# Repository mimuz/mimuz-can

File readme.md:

# mi:muz:can

`mi:muz-can` and variations are small boards for build easier to midi instrument that sounds cans using with push solenoid.

The following variations are exist:

## In Production

- [mi:muz:can (Standard Version)](./mimuz-can): "mi:muz:can" is a board for build easier to USB-MIDI instrument that sounds up to 6 cans using with push solenoid. For using powerful electric current, It has 2.1mm DC Jack for 12V DC Power supply.
- [mi:muz:can-lite](./mimuz-can-lite): "mi:muz:can-lite" is a board for build easier to USB-MIDI instrument that sounds up to 2 cans using with push solenoid. This is a "simple for use" version, It has micro-B usb connector for using USB charger for smartphone/tablet.

## demo

- [1st demo (YouTube)](https://youtu.be/6YQHXj_-I3c)

## Solenoids

All of the mi:muz:can devices are now only support the following 5V PUSH type solenoids:

- [Sparkfun Solenoid - 5v (small) (ROB-11015)](https://www.sparkfun.com/products/11015)
- [ZHO-0420S-05A4.5(5V)](http://akizukidenshi.com/catalog/g/gP-10761/)

## Licenses

- [Licences for mi:muz:can](./mimuz-can/LICENSE.md)
- [Licences for mi:muz:can-lite](./mimuz-can-lite/LICENSE.md)

## [Previous draft versions (Arduino versions)](./draft)

Previous draft versions (Arduino versions) are for experimental use versions made with [Arduino UNO Rev.3](https://store.arduino.cc/arduino-uno-rev3), [Ardiono Leonardo](https://www.arduino.cc/en/main/arduinoBoardLeonardo) and [mi:muz:expr#1](https://github.com/mimuz/mimuz-avr-core/tree/master/boards/expr1).

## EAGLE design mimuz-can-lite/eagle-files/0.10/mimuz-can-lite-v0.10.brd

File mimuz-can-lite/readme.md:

# mi:muz:can-lite

"mi:muz:can-lite" is a board for build easier to USB-MIDI instrument that sounds up to 2 cans using with push solenoid. This is a "simple for use" version, It has micro-B usb connector for using USB charger for smartphone/tablet.

## Version

- v0.10 (2017.05.10)

## Eagle Files

[eagle files (v0.10)](./eagle-files/v0.10)

## parts

- [STM32F042K6T6](http://www.st.com/content/st_com/ja/products/microcontrollers/stm32-32-bit-arm-cortex-mcus/stm32f0-series/stm32f0x2/stm32f042k6.html) * 1
- [HT7333-A (3.3V regulator) SOT89-3](http://www.holtek.com.tw/documents/10179/116711/HT73xx-1v100.pdf) * 1
- [Ferrite beads (0805)](http://akizukidenshi.com/catalog/g/gP-04054/) * 1 [ID1]
- 470Ω(0603) * 1 (For USB DATA LED)
- 1kΩ(0603) * 2 (For FET gate line)
- 1.5kΩ(0805) * 1 (For Power LED)
- 3mLED * 4 
- 0.1uF(0603) * 3
- 22uF(0805) * 1
- 47uF(1206 25V) * 1
- [Tactical Switch (2 points SMT)](http://www.aitendo.com/product/10525) * 1
- [micro USB Connector](https://www.aliexpress.com/item/Free-shipping-100pcs-lot-4-feet-DIP-5P-SMD-Micro-USB-Connector-V8-Port-Charge-Socket/32214653369.html?spm=2114.13010608.0.0.uwpujb) * 2
- PH2.0 2P Connector * 2
- 1N5819(DO214AC SMD) Shotkey diode * 2
- IRLML6344TRPBF SOT23 (Nch Mosfet) * 2

## Firmware

- [Source](../mimuz-can/source)
- [bin](./bin)

### Firmware Setup 

1. Install [SW4STM32](http://www.st.com/content/st_com/ja/products/development-tools/software-development-tools/stm32-software-development-tools/stm32-ides/sw4stm32.html)
2. Install DFU Loader (i.e. dfu-util see [dfu-util - Device Firmware Upgrade Utilities](http://dfu-util.sourceforge.net/))
3. Copy [Source](./source/mimuz-tuch) to your workspace path and select build target `mimuz-can-lite` and Bulding it. When your build process is succeed, `mimuz-can-lite.bin` is created in `./mimuz-can-lite/` folder.
4. push and hold mi:muz:can-lite board switch'BOOT0' switch and connect to USB Port. After connection, you can release switch. `mi:muz:can-lite` board will startup in DFU mode. 
5. Burn [mimuz-can-lite.bin] using DFU Loader. On Mac, enter the following command on terminal in same mimuz-can-lite.bin path.

> `dfu-util -a0 -d 0x0483:0xdf11 -s 0x008000000 -D mimuz-can.bin`

# Licenses

## Hardware (Schematics, Board, Eagle files), Software (Application, USB-MIDI Class Driver)

- [Creative Commons Attribution 4.0 International (CC BY 4.0)](http://creativecommons.org/licenses/by/4.0/)

## Software (STMCube from ST Microsystems)

- 3-clause BSD license

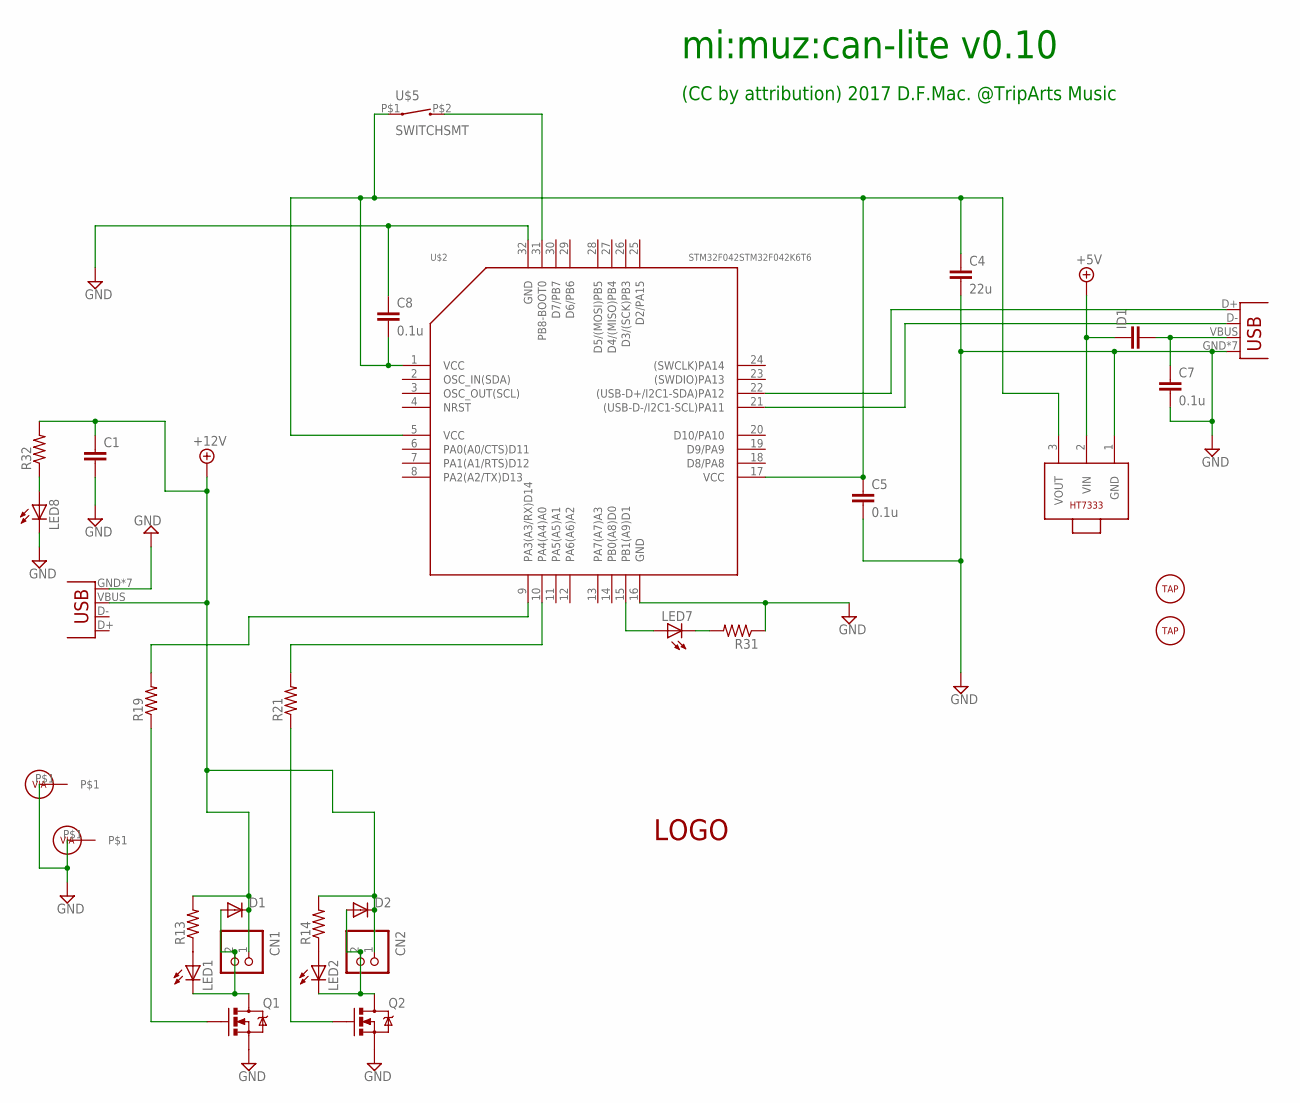
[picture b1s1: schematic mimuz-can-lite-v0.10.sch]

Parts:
C1: C-EUC1206; C1206
C4: 22u; C0805
C5, C7, C8: 0.1u; C0603
CN1, CN2: B2B-PH-K-S
D1, D2: DIODE-DO214AC; DO214AC
ID1: C-EUC0805; C0805
JP3, JP4: USB-MICROB
LED1, LED2, LED7, LED8: LED3MM
Q1, Q2: MOSFET-NCHANNELSMD; SOT23-3
R13, R14, R32: R-US_R0805; R0805
R19, R21, R31: R-US_R0603; R0603
U$1: LOGOSMALL; LOGO-SMALL
U$2: STM32F042STM32F042K6T6; TQFP32
U$3, U$6: TAPHOLE; TAPHOLE-3MM
U$4, U$7: VIA
U$5: SWITCHSMT; SWITCH-SMT-2*4*3
U$14: HT7333; SOT89

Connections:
3.3V: C4.1, C5.1, C8.2, U$2.1 (VCC), U$2.5 (VCC), U$2.17 (VCC), U$5.P$1 (1), U$14.3 (VOUT)
+5V: ID1.1, U$14.2 (VIN)
+5V2: C1.1, CN1.1, CN2.1, D1.C, D2.C, JP3.VBUS, R13.2, R14.2, R32.2
D+: JP4.D+, U$2.22 ((USB-D+/I2C1-SDA)PA12)
D-: JP4.D-, U$2.21 ((USB-D-/I2C1-SCL)PA11)
GND: C1.2, C4.2, C5.2, C7.2, C8.1, JP3.GND, JP3.MT1 (GND), JP3.MT3 (GND), JP3.P$2 (GND), JP3.P$4 (GND), JP3.P$5 (GND), JP3.P$6 (GND), JP4.GND, JP4.MT1 (GND), JP4.MT3 (GND), JP4.P$2 (GND), JP4.P$4 (GND), JP4.P$5 (GND), JP4.P$6 (GND), LED8.K (C), Q1.2 (S), Q2.2 (S), R31.1, U$2.16 (GND), U$2.32 (GND), U$4.P$1, U$7.P$1, U$14.1 (GND)
unnamed: LED7.A, U$2.15 (PB1(A9)D1)
unnamed: LED7.K (C), R31.2
unnamed: CN1.2, D1.A, LED1.K (C), Q1.3 (D)
unnamed: CN2.2, D2.A, LED2.K (C), Q2.3 (D)
unnamed: LED1.A, R13.1
unnamed: LED2.A, R14.1
unnamed: Q2.1 (G), R21.1
unnamed: Q1.1 (G), R19.1
unnamed: U$2.31 (PB8-BOOT0), U$5.P$2 (2)
unnamed: R19.2, U$2.9 (PA3(A3/RX)D14)
unnamed: R21.2, U$2.10 (PA4(A4)A0)
unnamed: LED8.A, R32.1
VBUS: C7.1, ID1.2, JP4.VBUS

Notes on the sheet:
mi:muz:can-lite v0.10
(CC by attribution) 2017 D.F.Mac. @TripArts Music

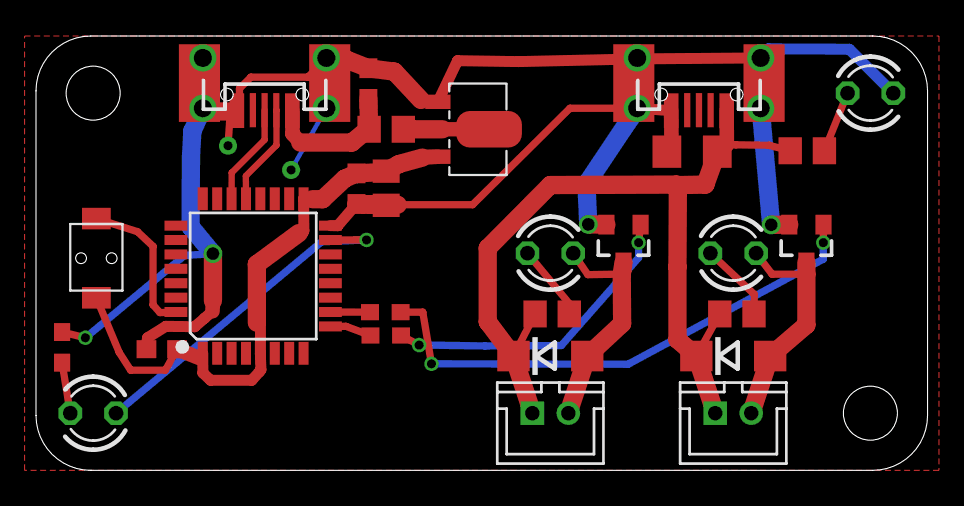
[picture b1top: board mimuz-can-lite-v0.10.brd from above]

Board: 2 copper layers, 49.5 x 24.1 mm, 32 parts (1 on the bottom side), 19 nets.

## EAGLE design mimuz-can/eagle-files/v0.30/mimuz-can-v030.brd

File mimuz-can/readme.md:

# mi:muz:can (Standard Version)

"mi:muz:can" is a board for build easier to USB-MIDI instrument that sounds up to 6 cans using with push solenoid. For using powerful electric current, It has 2.1mm DC Jack for 12V DC Power supply.

## Version

- v0.30 (2017.05.10)

## Eagle Files

[eagle files (v0.30)](./eagle-files/v0.30)

## parts

- [STM32F042K6T6](http://www.st.com/content/st_com/ja/products/microcontrollers/stm32-32-bit-arm-cortex-mcus/stm32f0-series/stm32f0x2/stm32f042k6.html) * 1
- [HT7333-A (3.3V regulator) SOT89-3](http://www.holtek.com.tw/documents/10179/116711/HT73xx-1v100.pdf) * 1
- [Ferrite beads (0805)](http://akizukidenshi.com/catalog/g/gP-04054/) * 1 [ID1]
- 470Ω(0603) * 1 (For USB DATA LED)
- 1kΩ(0603) * 6 (For FET gate line)
- 1.5kΩ(0805) * 1 (For Power LED)
- 2.2kΩ(0805) * 1 (For Power LED)
- 8.2Ω(2512 1W) * 12 (For Solenoid Line)
- 3mLED * 8 
- 0.1uF(0603) * 3
- 22uF(0805) * 1
- 47uF(1206 25V) * 1
- [Tactical Switch (2 points SMT)](http://www.aitendo.com/product/10525) * 1
- [micro USB Connector](https://www.aliexpress.com/item/Free-shipping-100pcs-lot-4-feet-DIP-5P-SMD-Micro-USB-Connector-V8-Port-Charge-Socket/32214653369.html?spm=2114.13010608.0.0.uwpujb) * 1
- [2.1mm DC Jack](http://akizukidenshi.com/catalog/g/gC-06568/) * 1
- PH2.0 2P Connector * 6
- 1N5819(DO214AC SMD) Shotkey diode * 6
- IRLML6344TRPBF SOT23 (Nch Mosfet) * 6

## Firmware

- [Source](./source)
- [bin](./bin)

### Firmware Setup 

1. Install [SW4STM32](http://www.st.com/content/st_com/ja/products/development-tools/software-development-tools/stm32-software-development-tools/stm32-ides/sw4stm32.html)
2. Install DFU Loader (i.e. dfu-util see [dfu-util - Device Firmware Upgrade Utilities](http://dfu-util.sourceforge.net/))
3. Copy [Source](./source/mimuz-tuch) to your workspace path and select build target `mimuz-can` and Bulding it. When your build process is succeed, `mimuz-can.bin` is created in `./mimuz-can/` folder.
4. push and hold mi:muz:can board switch'BOOT0' switch and connect to USB Port. After connection, you can release switch. `mi:muz:can` board will startup in DFU mode. 
5. Burn [mimuz-can.bin] using DFU Loader. On Mac, enter the following command on terminal in same mimuz-can.bin path.

> `dfu-util -a0 -d 0x0483:0xdf11 -s 0x008000000 -D mimuz-can.bin`

# Licenses

## Hardware (Schematics, Board, Eagle files), Software (Application, USB-MIDI Class Driver)

- [Creative Commons Attribution 4.0 International (CC BY 4.0)](http://creativecommons.org/licenses/by/4.0/)

## Software (STMCube from ST Microsystems)

- 3-clause BSD license

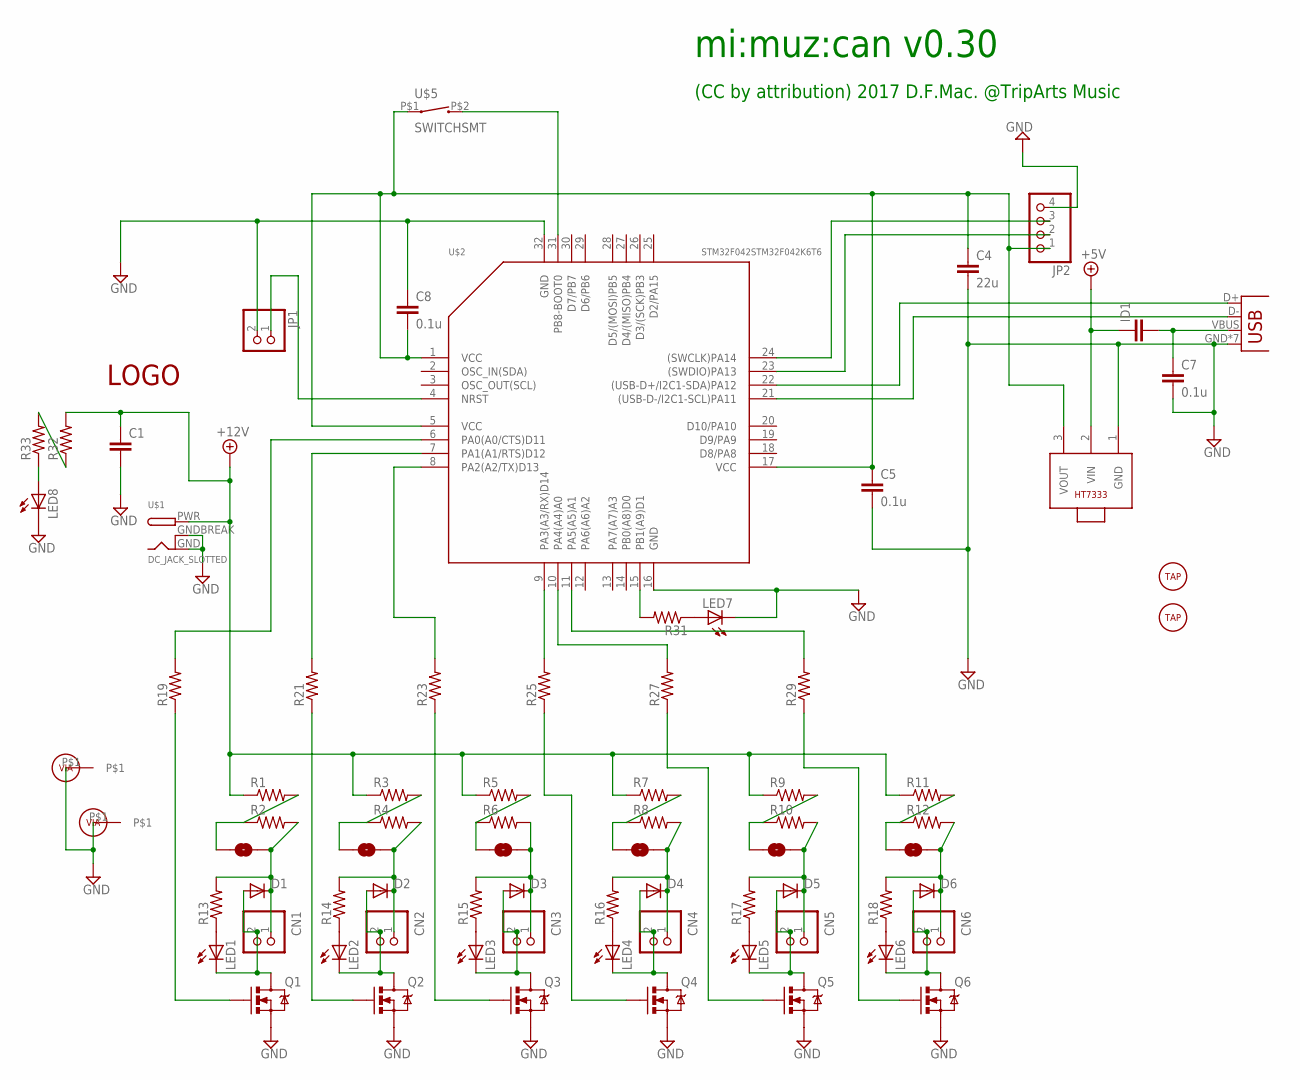
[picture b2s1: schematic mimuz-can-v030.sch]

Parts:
C1: C-EUC1206; C1206
C4: 22u; C0805
C5, C7, C8: 0.1u; C0603
CN1, CN2, CN3, CN4, CN5, CN6: B2B-PH-K-S
D1, D2, D3, D4, D5, D6: DIODE-DO214AC; DO214AC
ID1: C-EUC0805; C0805
JP1: PINHD-1X2; 1X02
JP2: PINHD-1X4; 1X04
JP3, JP5, JP6, JP7, JP8, JP9: JUMPER-SMT_2_NO_NO-SILK; SMT-JUMPER_2_NO_NO-SILK
JP4: USB-MICROB
LED1, LED2, LED3, LED4, LED5, LED6, LED7, LED8: LED3MM
Q1, Q2, Q3, Q4, Q5, Q6: MOSFET-NCHANNELSMD; SOT23-3
R1, R2, R3, R4, R5, R6, R7, R8, R9, R10, R11, R12: R-US_R2512; R2512
R13, R14, R15, R16, R17, R18, R32, R33: R-US_R0805; R0805
R19, R21, R23, R25, R27, R29, R31: R-US_R0603; R0603
U$1: DC_JACK_SLOTTED
U$2: STM32F042STM32F042K6T6; TQFP32
U$3, U$6: TAPHOLE; TAPHOLE-3MM
U$4, U$7: VIA
U$5: SWITCHSMT; SWITCH-SMT-2*4*3
U$12: LOGOSMALL; LOGO-SMALL
U$14: HT7333; SOT89

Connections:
3.3V: C4.1, C5.1, C8.2, JP2.1, U$2.1 (VCC), U$2.5 (VCC), U$2.17 (VCC), U$5.P$1 (1), U$14.3 (VOUT)
+5V: ID1.1, U$14.2 (VIN)
+12V: C1.1, R1.1, R3.1, R5.1, R7.1, R9.1, R11.1, R32.2, U$1.PWR
D+: JP4.D+, U$2.22 ((USB-D+/I2C1-SDA)PA12)
D-: JP4.D-, U$2.21 ((USB-D-/I2C1-SCL)PA11)
GND: C1.2, C4.2, C5.2, C7.2, C8.1, JP1.2, JP2.4, JP4.GND, JP4.MT1 (GND), JP4.MT3 (GND), JP4.P$2 (GND), JP4.P$4 (GND), JP4.P$5 (GND), JP4.P$6 (GND), LED7.K (C), LED8.K (C), Q1.2 (S), Q2.2 (S), Q3.2 (S), Q4.2 (S), Q5.2 (S), Q6.2 (S), U$1.GND, U$1.GNDBREAK, U$2.16 (GND), U$2.32 (GND), U$4.P$1, U$7.P$1, U$14.1 (GND)
unnamed: JP5.1, R3.2, R4.1
unnamed: JP3.1, R1.2, R2.1
unnamed: JP6.1, R5.2, R6.1
unnamed: CN1.1, D1.C, JP3.2, R2.2, R13.2
unnamed: CN2.1, D2.C, JP5.2, R4.2, R14.2
unnamed: CN3.1, D3.C, JP6.2, R6.2, R15.2
unnamed: CN1.2, D1.A, LED1.K (C), Q1.3 (D)
unnamed: CN2.2, D2.A, LED2.K (C), Q2.3 (D)
unnamed: CN3.2, D3.A, LED3.K (C), Q3.3 (D)
unnamed: JP7.1, R7.2, R8.1
unnamed: CN4.1, D4.C, JP7.2, R8.2, R16.2
unnamed: CN4.2, D4.A, LED4.K (C), Q4.3 (D)
unnamed: CN5.2, D5.A, LED5.K (C), Q5.3 (D)
unnamed: CN6.2, D6.A, LED6.K (C), Q6.3 (D)
unnamed: JP8.1, R9.2, R10.1
unnamed: JP9.1, R11.2, R12.1
unnamed: LED1.A, R13.1
unnamed: CN6.1, D6.C, JP9.2, R12.2, R18.2
unnamed: CN5.1, D5.C, JP8.2, R10.2, R17.2
unnamed: LED2.A, R14.1
unnamed: LED3.A, R15.1
unnamed: LED4.A, R16.1
unnamed: Q2.1 (G), R21.1
unnamed: Q1.1 (G), R19.1
unnamed: LED5.A, R17.1
unnamed: Q3.1 (G), R23.1
unnamed: JP2.3, U$2.24 ((SWCLK)PA14)
unnamed: JP2.2, U$2.23 ((SWDIO)PA13)
unnamed: JP1.1, U$2.4 (NRST)
unnamed: U$2.31 (PB8-BOOT0), U$5.P$2 (2)
unnamed: LED6.A, R18.1
unnamed: R19.2, U$2.6 (PA0(A0/CTS)D11)
unnamed: R21.2, U$2.7 (PA1(A1/RTS)D12)
unnamed: R23.2, U$2.8 (PA2(A2/TX)D13)
unnamed: R27.2, U$2.10 (PA4(A4)A0)
unnamed: R25.2, U$2.9 (PA3(A3/RX)D14)
unnamed: Q4.1 (G), R25.1
unnamed: Q5.1 (G), R27.1
unnamed: R29.2, U$2.11 (PA5(A5)A1)
unnamed: Q6.1 (G), R29.1
unnamed: R31.2, U$2.15 (PB1(A9)D1)
unnamed: LED7.A, R31.1
unnamed: R32.1, R33.2
unnamed: LED8.A, R33.1
VBUS: C7.1, ID1.2, JP4.VBUS

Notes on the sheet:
mi:muz:can v0.30
(CC by attribution) 2017 D.F.Mac. @TripArts Music

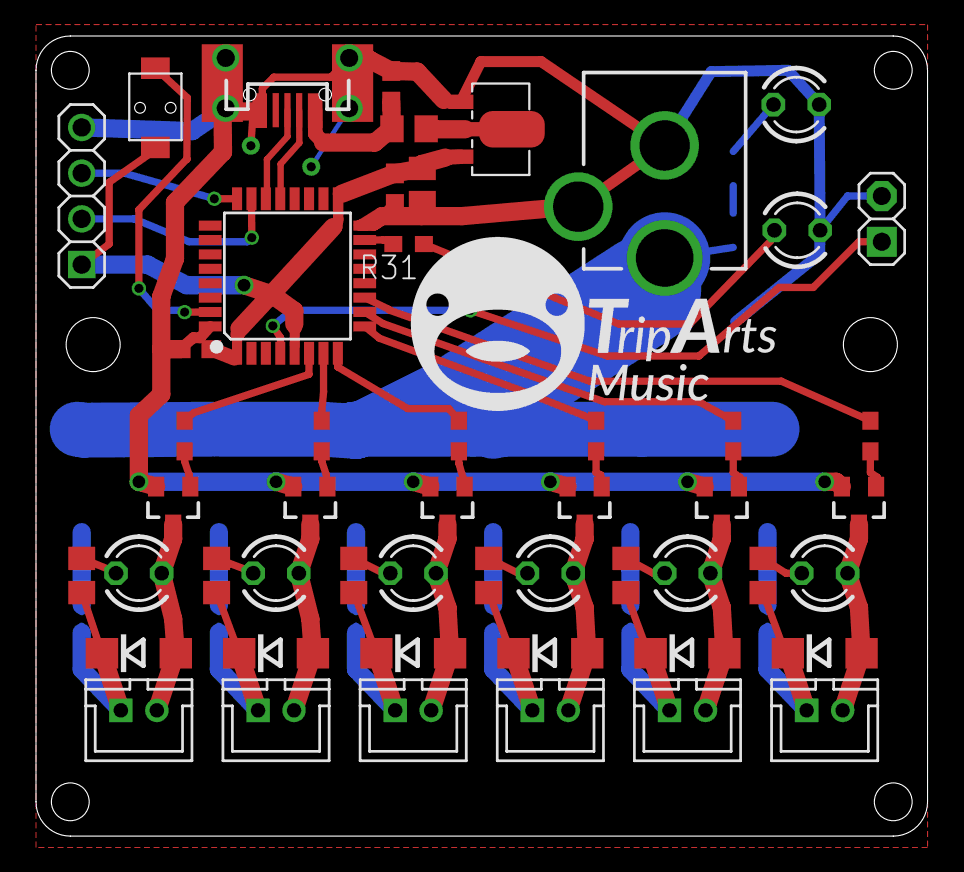
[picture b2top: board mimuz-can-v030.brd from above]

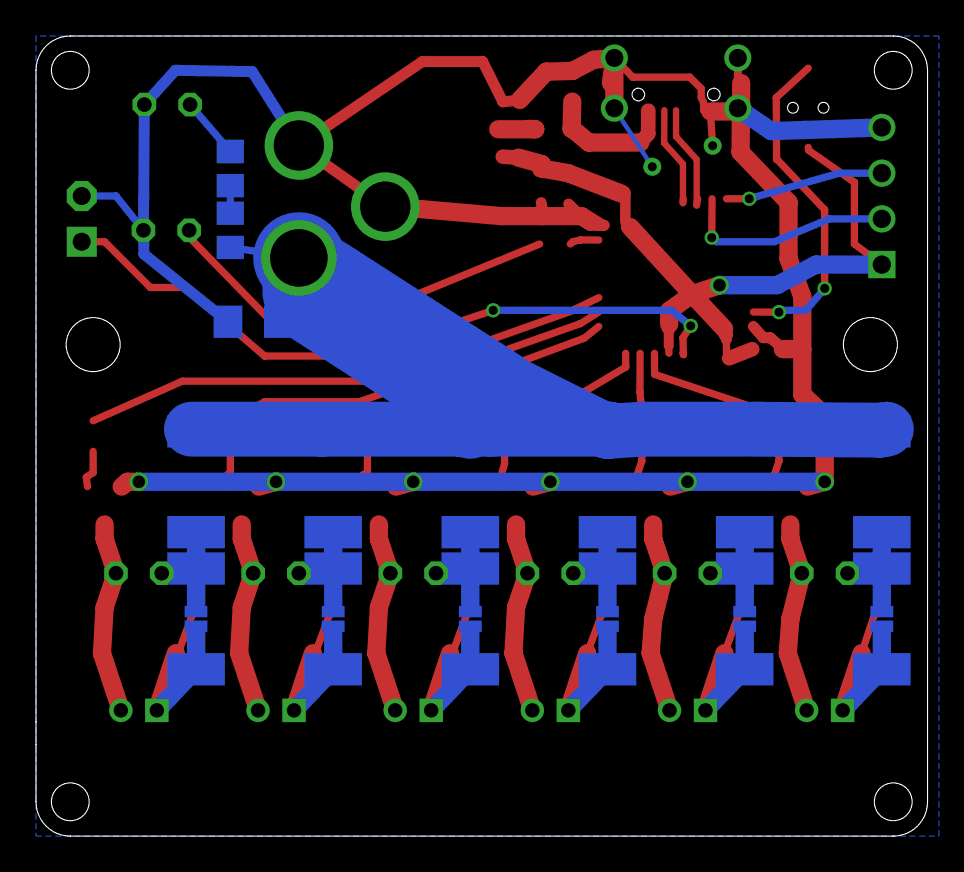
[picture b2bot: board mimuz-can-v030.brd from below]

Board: 2 copper layers, 49.5 x 44.5 mm, 77 parts (21 on the bottom side), 51 nets.

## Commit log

2017-05-02 fix path
2017-05-10 update documents
2017-05-10 update license info
2017-05-10 fix readme.md
2017-05-10 rename folder name
2017-05-10 add system configulation artwork
2017-05-10 add link to demo
2017-05-10 add mi:muz:can files
2017-05-10 add mi:muz:can-lite files

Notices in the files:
parts and their libraries:
SparkFun-Jumpers: Licensing: Creative Commons ShareAlike 4.0 International - https://creativecommons.org/licenses/by-sa/4.0
